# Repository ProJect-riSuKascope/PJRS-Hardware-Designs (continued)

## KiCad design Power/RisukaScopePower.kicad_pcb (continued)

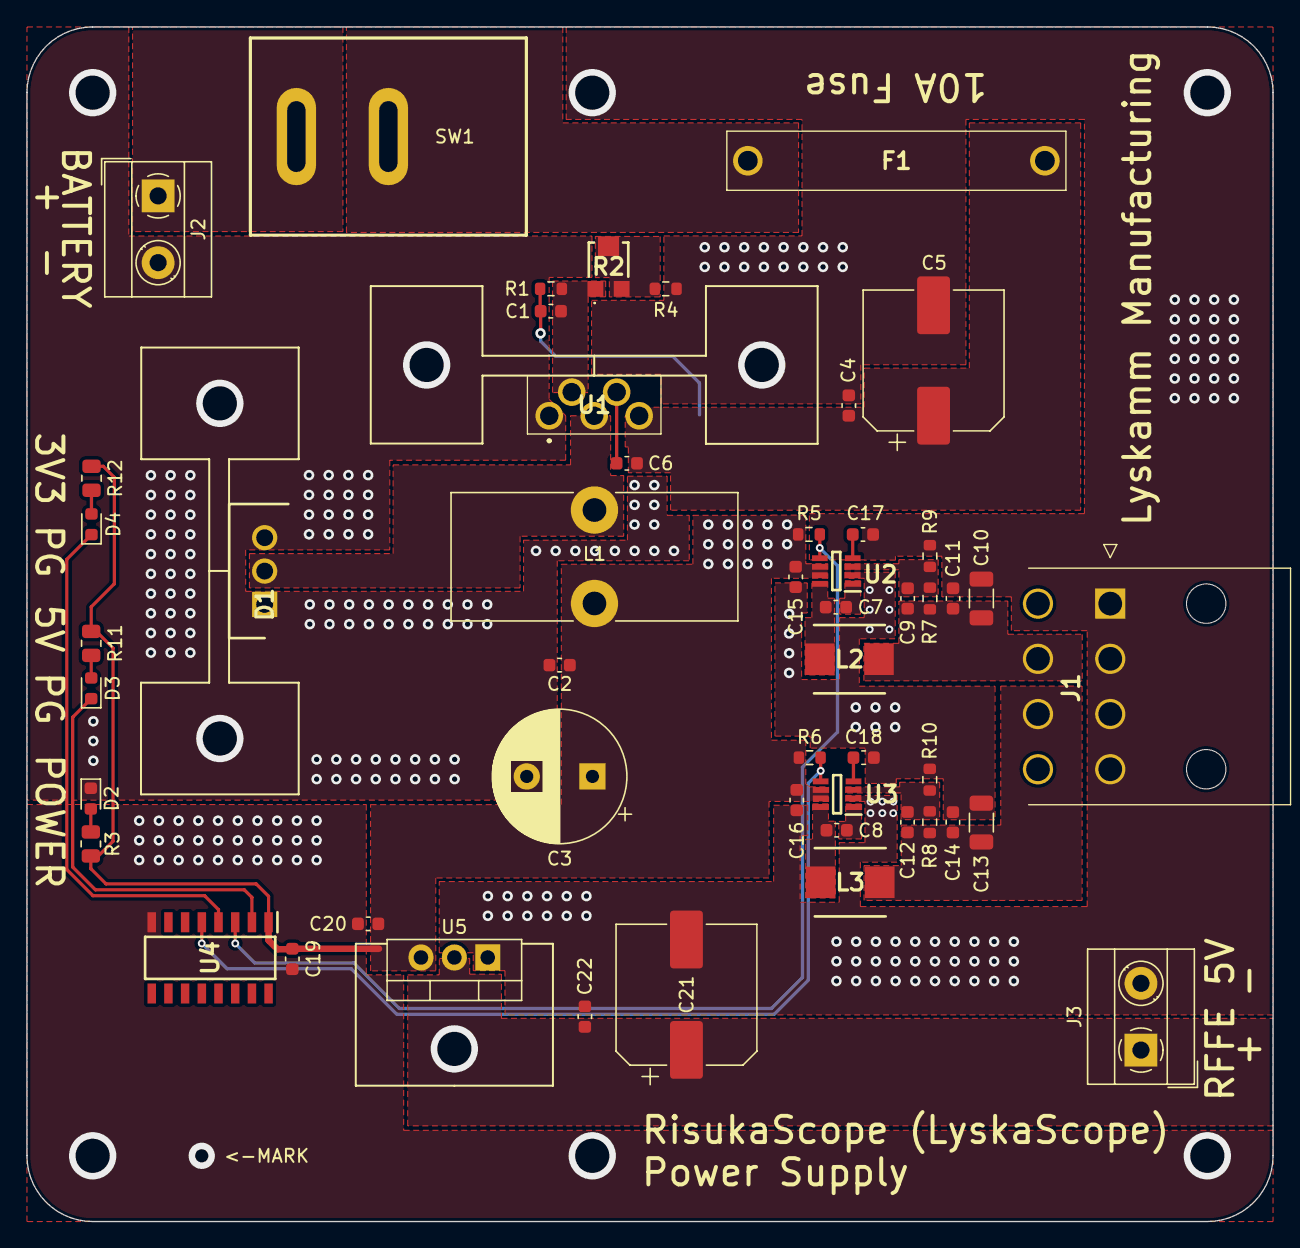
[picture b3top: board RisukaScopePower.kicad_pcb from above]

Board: 2 copper layers, 94.8 x 90.9 mm, 51 parts (0 on the bottom side), 27 nets.

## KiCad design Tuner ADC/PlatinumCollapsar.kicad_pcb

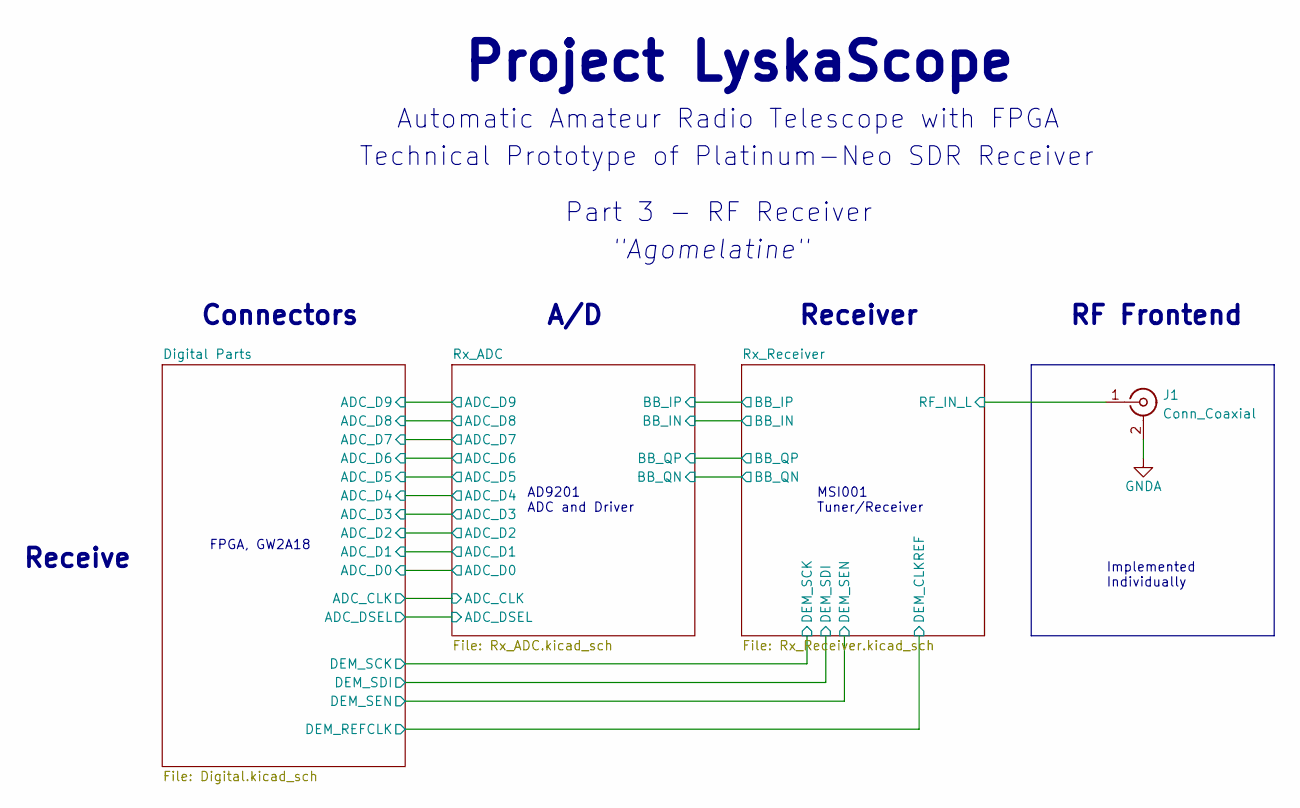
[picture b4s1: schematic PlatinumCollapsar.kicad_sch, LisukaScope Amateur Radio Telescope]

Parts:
J1: Conn_Coaxial; SMA_Samtec_SMA-J-P-X-ST-EM1_EdgeMount

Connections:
/Rx_Receiver/RF_IN_L: J1.1 (In); also elsewhere on the board

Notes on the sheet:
Connectors
Receive
FPGA, GW2A18
Technical Prototype of Platinum-Neo SDR Receiver
AD9201 ADC and Driver
Project LyskaScope
Receiver
Automatic Amateur Radio Telescope with FPGA
MSI001 Tuner/Receiver
Implemented Individually
RF Frontend
A/D
"Agomelatine"
Part 3 - RF Receiver

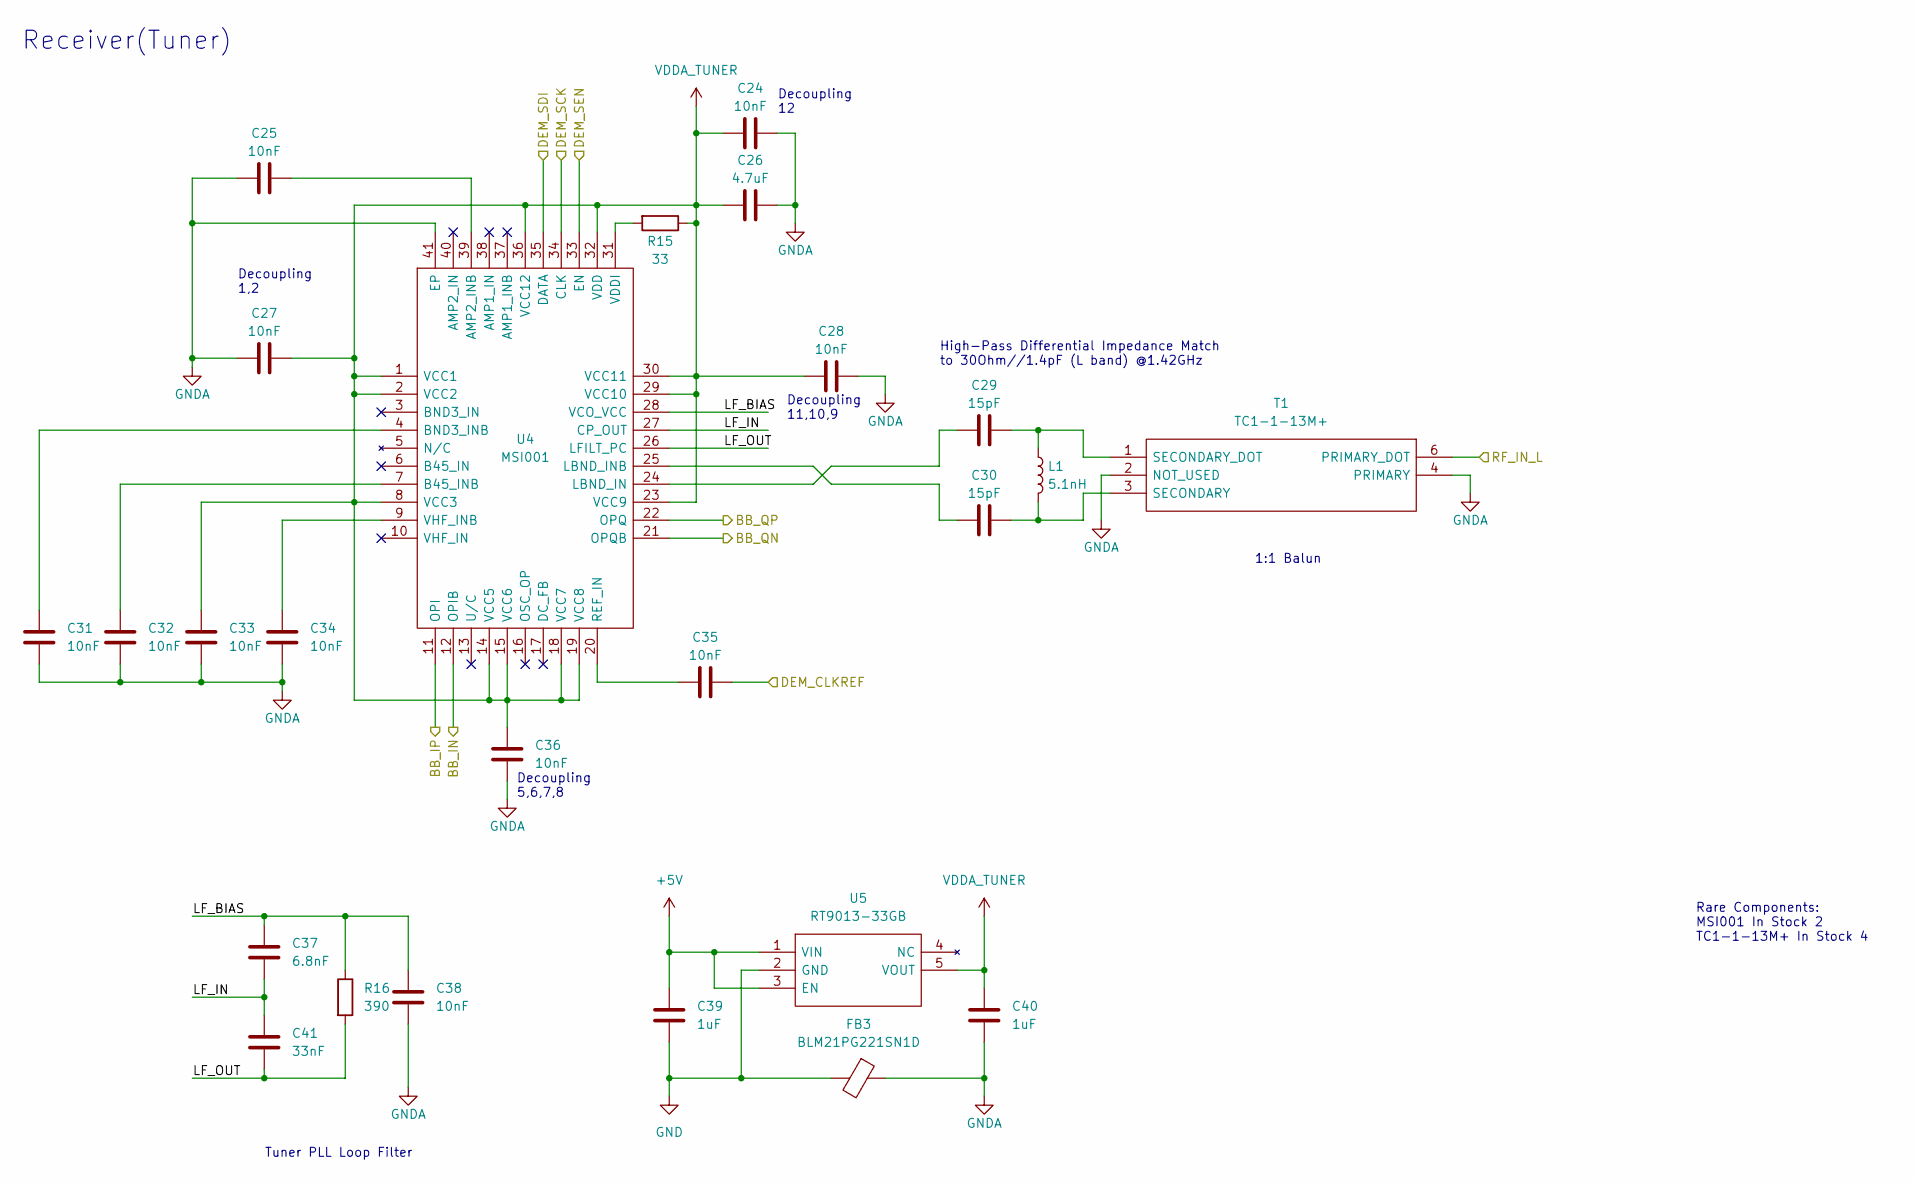
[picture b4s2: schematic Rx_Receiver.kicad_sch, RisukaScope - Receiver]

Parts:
C24, C25, C27, C28, C31, C32, C33, C34, C35, C36, C38: 10nF; C_0603_1608Metric
C26: 4.7uF; C_0603_1608Metric
C29, C30: 15pF; C_0603_1608Metric
C37: 6.8nF; C_0603_1608Metric
C39, C40: 1uF; C_0603_1608Metric
C41: 33nF; C_0603_1608Metric
FB3: BLM21PG221SN1D; L_0805_2012Metric
L1: 5.1nH; L_0603_1608Metric
R15: 33; R_0603_1608Metric
R16: 390; R_0603_1608Metric
T1: TC1-1-13M+; TC414; Manufacturer_Part_Number TC1-1-13M+; Mouser Part Number 139-TC1-1-13M
U4: MSI001; QFN50P600X600X90-41N-D; Manufacturer_Part_Number MSI001
U5: RT9013-33GB; SOT94P279X130-5N; Manufacturer_Part_Number RT9013-33GB

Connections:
+5V: C39.1, U5.1 (VIN), U5.3 (EN); also elsewhere on the board
/Digital Parts/DEM_REFCLK: C35.2; also elsewhere on the board
/Digital Parts/DEM_SCK: U4.34 (CLK); also elsewhere on the board
/Digital Parts/DEM_SDI: U4.35 (DATA); also elsewhere on the board
/Digital Parts/DEM_SEN: U4.33 (EN); also elsewhere on the board
/Rx_ADC/BB_IN: U4.12 (OPIB); also elsewhere on the board
/Rx_ADC/BB_IP: U4.11 (OPI); also elsewhere on the board
/Rx_ADC/BB_QN: U4.21 (OPQB); also elsewhere on the board
/Rx_ADC/BB_QP: U4.22 (OPQ); also elsewhere on the board
/Rx_Receiver/LF_BIAS: C37.1, C38.1, R16.1, U4.28 (VCO_VCC)
/Rx_Receiver/LF_IN: C37.2, C41.1, U4.27 (CP_OUT)
/Rx_Receiver/LF_OUT: C41.2, R16.2, U4.26 (LFILT_PC)
/Rx_Receiver/RF_IN_L: T1.6 (PRIMARY_DOT); also elsewhere on the board
GND: C39.2, FB3.2, U5.2 (GND); also elsewhere on the board
unnamed: C25.2, U4.39 (AMP2_INB)
unnamed: C29.1, U4.24 (LBND_IN)
unnamed: C29.2, L1.1, T1.1 (SECONDARY_DOT)
unnamed: C30.1, U4.25 (LBND_INB)
unnamed: C30.2, L1.2, T1.3 (SECONDARY)
unnamed: C31.1, U4.4 (BND3_INB)
unnamed: C32.1, U4.7 (B45_INB)
unnamed: C34.1, U4.9 (VHF_INB)
unnamed: C35.1, U4.20 (REF_IN)
unnamed: R15.2, U4.31 (VDDI)
VDDA_TUNER: C24.1, C26.1, C27.2, C28.1, C33.1, C36.1, C40.1, R15.1, U4.1 (VCC1), U4.2 (VCC2), U4.8 (VCC3), U4.14 (VCC5), U4.15 (VCC6), U4.18 (VCC7), U4.19 (VCC8), U4.23 (VCC9), U4.29 (VCC10), U4.30 (VCC11), U4.32 (VDD), U4.36 (VCC12), U5.5 (VOUT)

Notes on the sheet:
Decoupling 12
Decoupling 11,10,9
1:1 Balun
Receiver(Tuner)
Decoupling 5,6,7,8
Tuner PLL Loop Filter
High-Pass Differential Impedance Match to 30Ohm//1.4pF (L band) @1.42GHz
Rare Components: MSI001 In Stock 2 TC1-1-13M+ In Stock 4
Decoupling 1,2

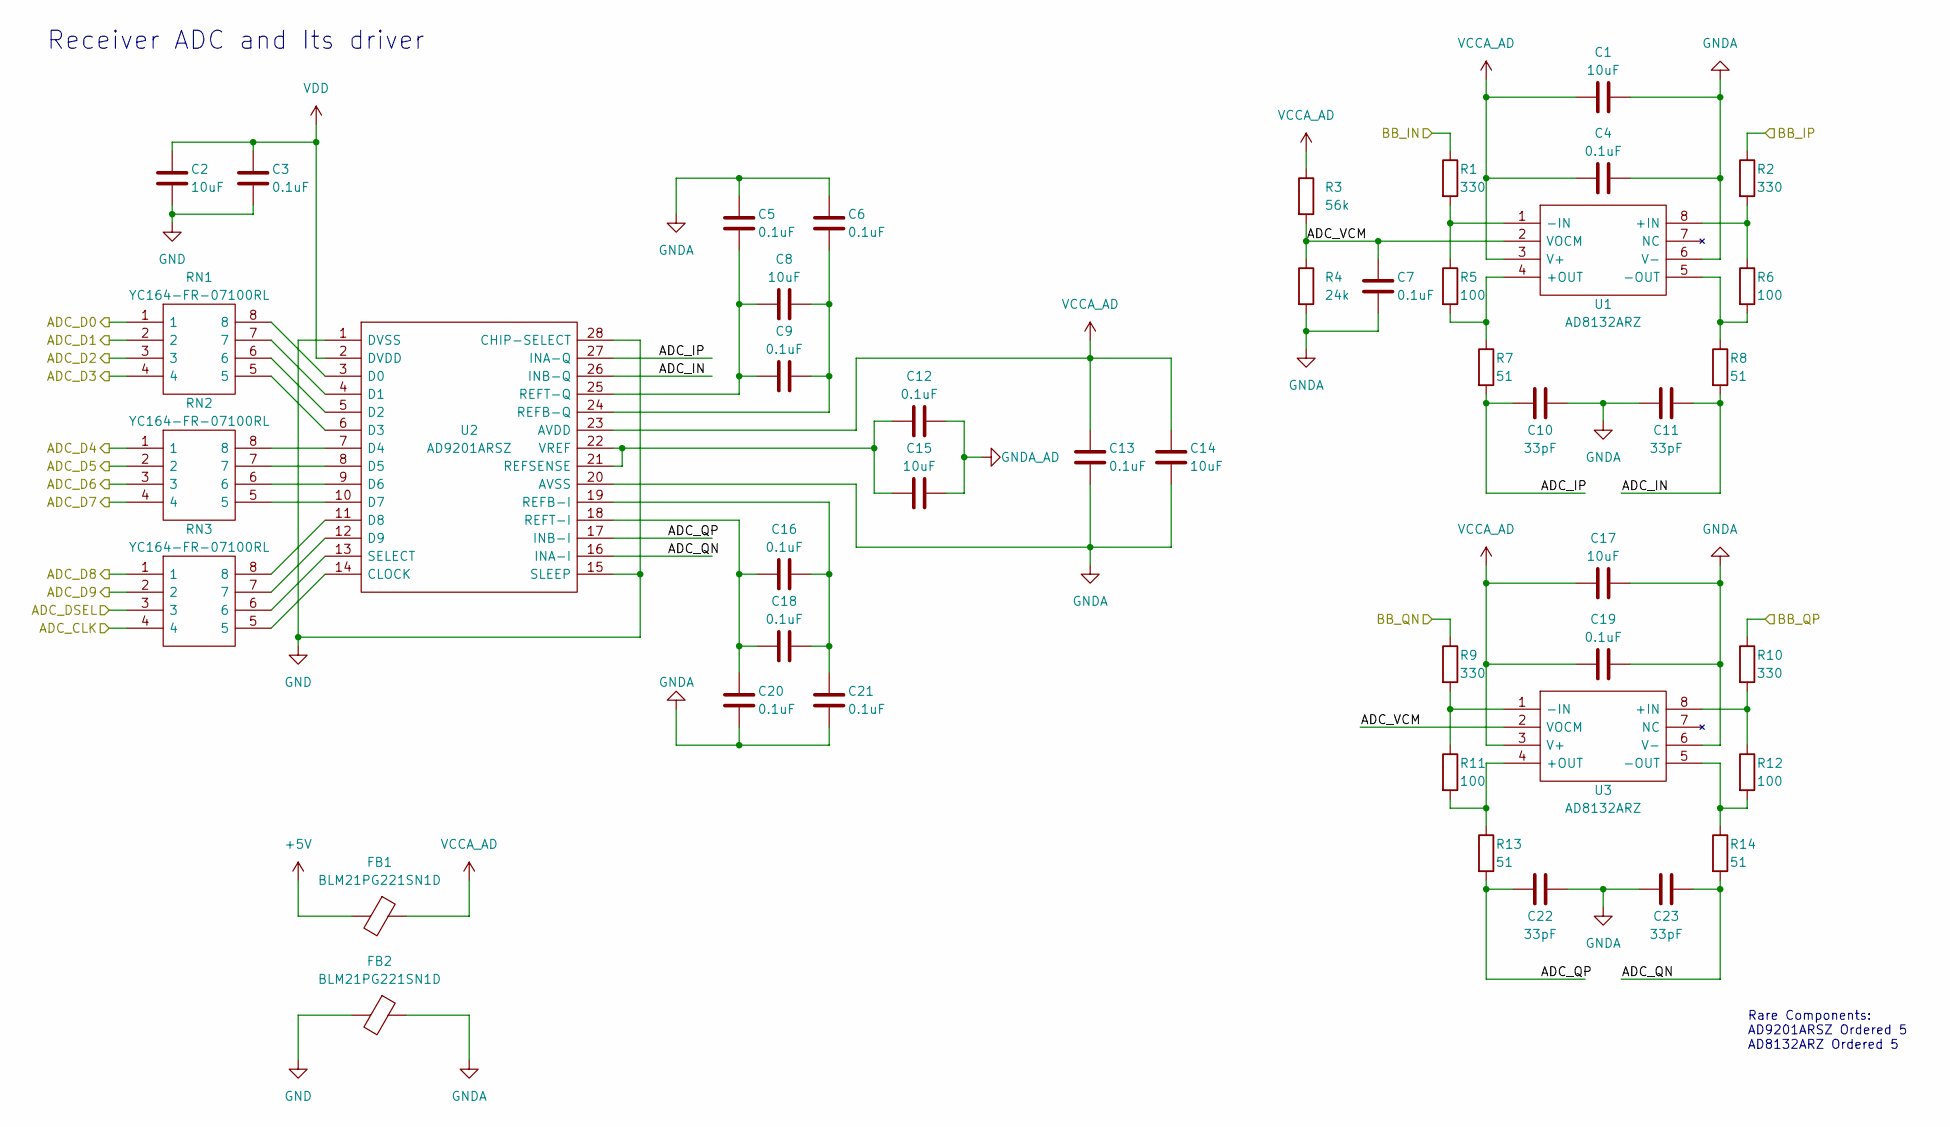
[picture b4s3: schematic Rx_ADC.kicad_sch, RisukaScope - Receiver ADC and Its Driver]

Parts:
C1, C2, C8, C14, C15, C17: 10uF; C_0603_1608Metric
C3, C4, C5, C6, C7, C9, C12, C13, C16, C18, C19, C20, C21: 0.1uF; C_0603_1608Metric
C10, C11, C22, C23: 33pF; C_0603_1608Metric
FB1, FB2: BLM21PG221SN1D; L_0805_2012Metric
R1, R2, R9, R10: 330; R_0603_1608Metric
R3: 56k; R_0603_1608Metric
R4: 24k; R_0603_1608Metric
R5, R6, R11, R12: 100; R_0603_1608Metric
R7, R8, R13, R14: 51; R_0603_1608Metric
RN1, RN2, RN3: YC164-FR-07100RL; YC164JR07220RL; Manufacturer_Part_Number YC164-FR-07100RL; Mouser Part Number 603-YC164-FR-07100RL
U1, U3: AD8132ARZ; SOIC127P600X175-8N; Manufacturer_Part_Number AD8132ARZ; Mouser Part Number 584-AD8132ARZ
U2: AD9201ARSZ; SOP65P777X198-28N; Manufacturer_Part_Number AD9201ARSZ; Mouser Part Number 584-AD9201ARSZ

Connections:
+5V: FB1.2; also elsewhere on the board
/Digital Parts/ADC_CLK: RN3.4; also elsewhere on the board
/Digital Parts/ADC_D0: RN1.1; also elsewhere on the board
/Digital Parts/ADC_D1: RN1.2; also elsewhere on the board
/Digital Parts/ADC_D2: RN1.3; also elsewhere on the board
/Digital Parts/ADC_D3: RN1.4; also elsewhere on the board
/Digital Parts/ADC_D4: RN2.1; also elsewhere on the board
/Digital Parts/ADC_D5: RN2.2; also elsewhere on the board
/Digital Parts/ADC_D6: RN2.3; also elsewhere on the board
/Digital Parts/ADC_D7: RN2.4; also elsewhere on the board
/Digital Parts/ADC_D8: RN3.1; also elsewhere on the board
/Digital Parts/ADC_D9: RN3.2; also elsewhere on the board
/Digital Parts/ADC_DSEL: RN3.3; also elsewhere on the board
/Rx_ADC/ADC_IN: C11.2, R8.2, U2.26 (INB-Q)
/Rx_ADC/ADC_IP: C10.1, R7.2, U2.27 (INA-Q)
/Rx_ADC/ADC_QN: C23.2, R14.2, U2.16 (INA-I)
/Rx_ADC/ADC_QP: C22.1, R13.2, U2.17 (INB-I)
/Rx_ADC/ADC_VCM: C7.1, R3.2, R4.1, U1.2 (VOCM), U3.2 (VOCM)
/Rx_ADC/BB_IN: R1.1; also elsewhere on the board
/Rx_ADC/BB_IP: R2.1; also elsewhere on the board
/Rx_ADC/BB_QN: R9.1; also elsewhere on the board
/Rx_ADC/BB_QP: R10.1; also elsewhere on the board
GND: C2.2, C3.2, FB2.2, U2.1 (DVSS), U2.15 (SLEEP), U2.28 (CHIP-SELECT); also elsewhere on the board
unnamed: C5.2, C8.1, C9.1, U2.25 (REFT-Q)
unnamed: C6.2, C8.2, C9.2, U2.24 (REFB-Q)
unnamed: C12.1, C15.1, U2.21 (REFSENSE), U2.22 (VREF)
unnamed: C16.1, C18.1, C20.1, U2.18 (REFT-I)
unnamed: C16.2, C18.2, C21.1, U2.19 (REFB-I)
unnamed: R1.2, R5.1, U1.1 (-IN)
unnamed: R2.2, R6.1, U1.8 (+IN)
unnamed: R5.2, R7.1, U1.4 (+OUT)
unnamed: R6.2, R8.1, U1.5 (-OUT)
unnamed: R10.2, R12.1, U3.8 (+IN)
unnamed: R9.2, R11.1, U3.1 (-IN)
unnamed: R11.2, R13.1, U3.4 (+OUT)
unnamed: R12.2, R14.1, U3.5 (-OUT)
unnamed: RN1.5, U2.6 (D3)
unnamed: RN1.6, U2.5 (D2)
unnamed: RN1.7, U2.4 (D1)
unnamed: RN1.8, U2.3 (D0)
unnamed: RN2.5, U2.10 (D7)
unnamed: RN2.6, U2.9 (D6)
unnamed: RN2.7, U2.8 (D5)
unnamed: RN2.8, U2.7 (D4)
unnamed: RN3.5, U2.14 (CLOCK)
unnamed: RN3.6, U2.13 (SELECT)
unnamed: RN3.7, U2.12 (D9)
unnamed: RN3.8, U2.11 (D8)
VCCA_AD: C1.1, C4.1, C13.1, C14.1, C17.1, C19.1, FB1.1, R3.1, U1.3 (V+), U2.23 (AVDD), U3.3 (V+)
VDD: C2.1, C3.1, U2.2 (DVDD); also elsewhere on the board

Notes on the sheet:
Rare Components: AD9201ARSZ Ordered 5 AD8132ARZ Ordered 5
Receiver ADC and Its driver

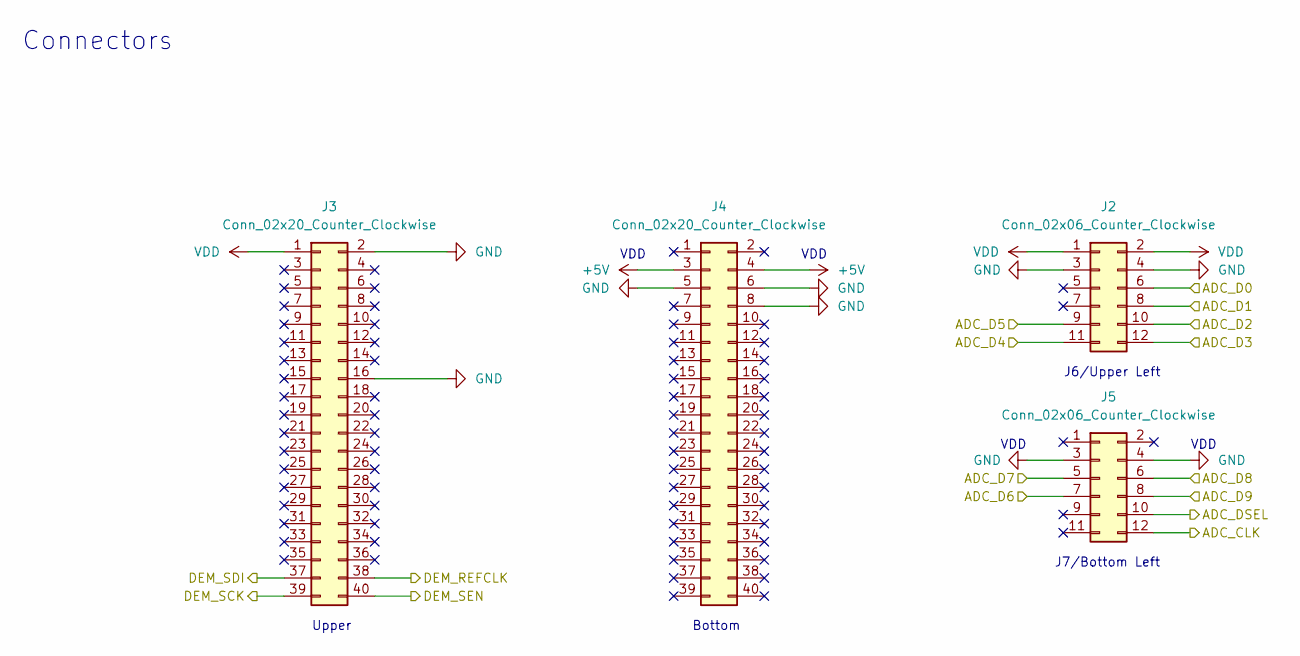
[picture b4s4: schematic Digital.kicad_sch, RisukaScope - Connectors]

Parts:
J2, J5: Conn_02x06_Counter_Clockwise; PinHeader_2x06_P2.54mm_Vertical
J3, J4: Conn_02x20_Counter_Clockwise; PinHeader_2x20_P2.54mm_Vertical

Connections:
+5V: J4.3, J4.4; also elsewhere on the board
/Digital Parts/ADC_CLK: J5.12; also elsewhere on the board
/Digital Parts/ADC_D0: J2.6; also elsewhere on the board
/Digital Parts/ADC_D1: J2.8; also elsewhere on the board
/Digital Parts/ADC_D2: J2.10; also elsewhere on the board
/Digital Parts/ADC_D3: J2.12; also elsewhere on the board
/Digital Parts/ADC_D4: J2.11; also elsewhere on the board
/Digital Parts/ADC_D5: J2.9; also elsewhere on the board
/Digital Parts/ADC_D6: J5.7; also elsewhere on the board
/Digital Parts/ADC_D7: J5.5; also elsewhere on the board
/Digital Parts/ADC_D8: J5.6; also elsewhere on the board
/Digital Parts/ADC_D9: J5.8; also elsewhere on the board
/Digital Parts/ADC_DSEL: J5.10; also elsewhere on the board
/Digital Parts/DEM_REFCLK: J3.38; also elsewhere on the board
/Digital Parts/DEM_SCK: J3.39; also elsewhere on the board
/Digital Parts/DEM_SDI: J3.37; also elsewhere on the board
/Digital Parts/DEM_SEN: J3.40; also elsewhere on the board
GND: J2.3, J2.4, J3.2, J3.16, J4.5, J4.6, J4.8, J5.3, J5.4; also elsewhere on the board
VDD: J2.1, J2.2, J3.1; also elsewhere on the board

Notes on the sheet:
Upper
J7/Bottom Left
VDD
J6/Upper Left
Connectors
Bottom

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
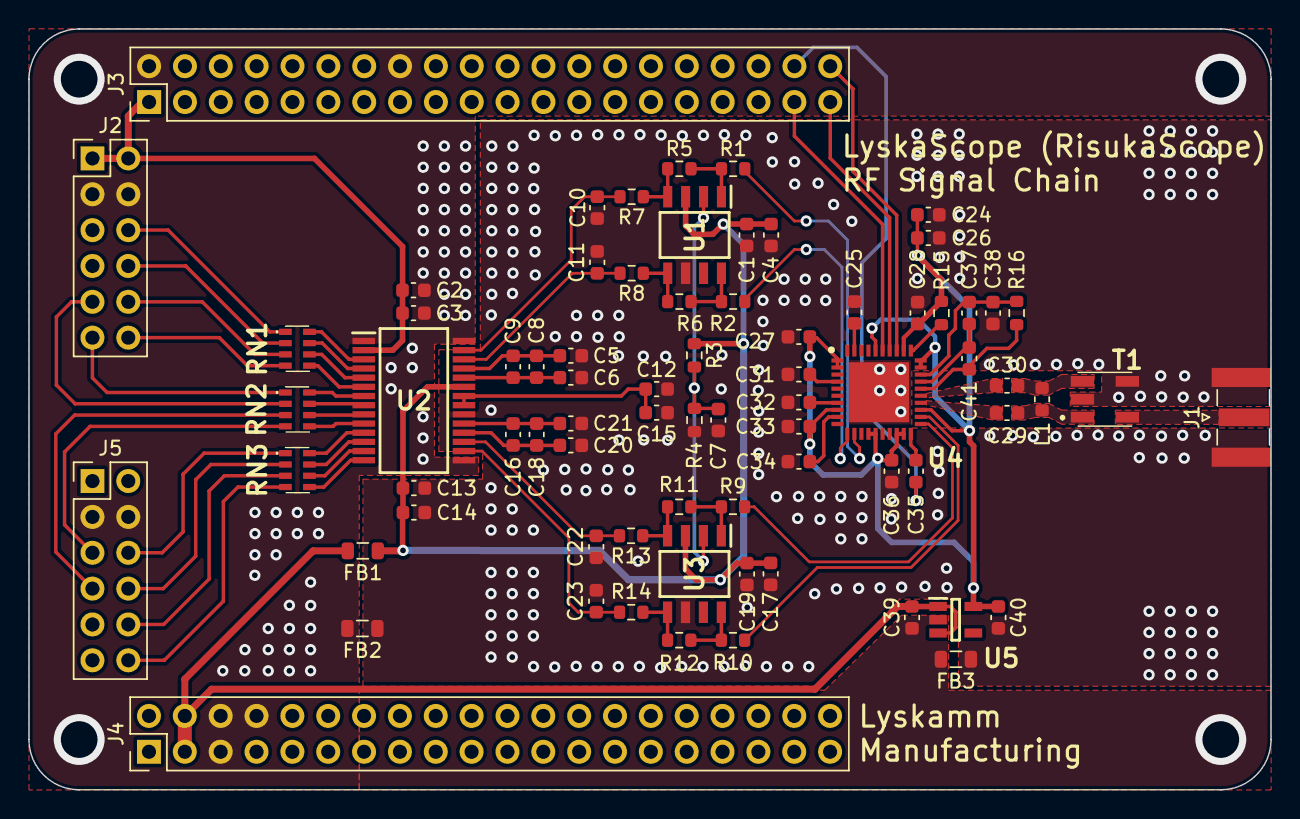
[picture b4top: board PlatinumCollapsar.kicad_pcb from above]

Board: 2 copper layers, 88.0 x 53.9 mm, 75 parts (0 on the bottom side), 70 nets.

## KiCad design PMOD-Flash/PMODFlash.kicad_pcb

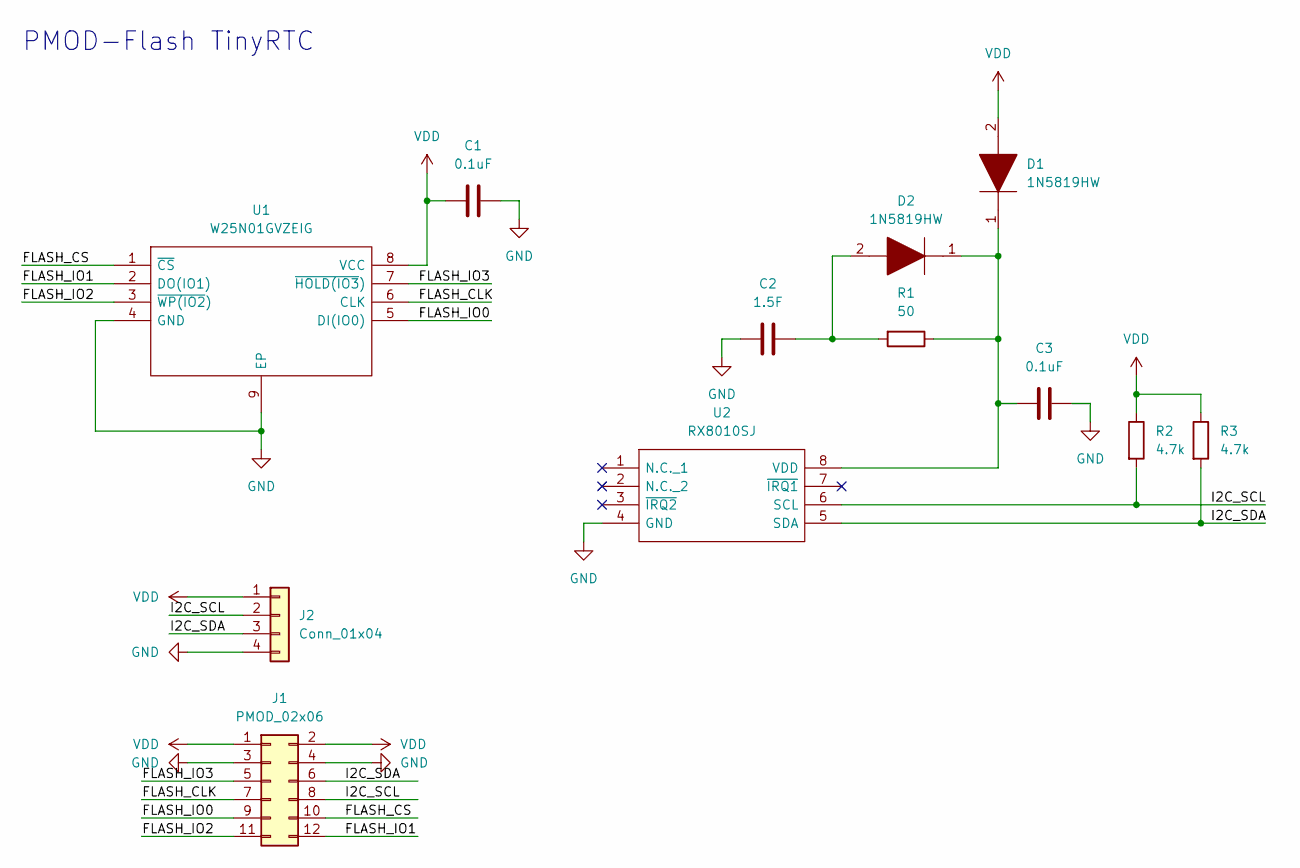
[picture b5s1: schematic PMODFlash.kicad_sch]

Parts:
C1, C3: 0.1uF; C_0603_1608Metric
C2: 1.5F; EECS5R5V155N
D1, D2: 1N5819HW; SOD3716X145N; Manufacturer_Part_Number 1N5819HW; Mouser Part Number N/A
J1: PMOD_02x06; PinHeader_2x06_P2.54mm_Vertical
J2: Conn_01x04; PinHeader_1x04_P2.54mm_Vertical
R1: 50; R_0603_1608Metric
R2, R3: 4.7k; R_0603_1608Metric
U1: W25N01GVZEIG; SON127P800X600X80-9N-D; Manufacturer_Part_Number W25N01GVZEIG; Mouser Part Number 454-W25N01GVZEIG
U2: RX8010SJ; SOIC127P600X265-8N; Manufacturer_Part_Number RX8010SJ

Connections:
/FLASH_CLK: J1.7, U1.6 (CLK)
/FLASH_CS: J1.10, U1.1 (~CS)
/FLASH_IO0: J1.9, U1.5 (DI(IO0))
/FLASH_IO1: J1.12, U1.2 (DO(IO1))
/FLASH_IO2: J1.11, U1.3 (~WP(IO2))
/FLASH_IO3: J1.5, U1.7 (~HOLD(IO3))
/I2C_SCL: J1.8, J2.2, R2.2, U2.6 (SCL)
/I2C_SDA: J1.6, J2.3, R3.2, U2.5 (SDA)
GND: C1.1, C2.2, C3.1, J1.3, J1.4, J2.4, U1.4 (GND), U1.9 (EP), U2.4 (GND)
unnamed: C2.1, D2.2, R1.2
unnamed: C3.2, D1.1, D2.1, R1.1, U2.8 (VDD)
VDD: C1.2, D1.2, J1.1, J1.2, J2.1, R2.1, R3.1, U1.8 (VCC)

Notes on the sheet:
PMOD-Flash TinyRTC

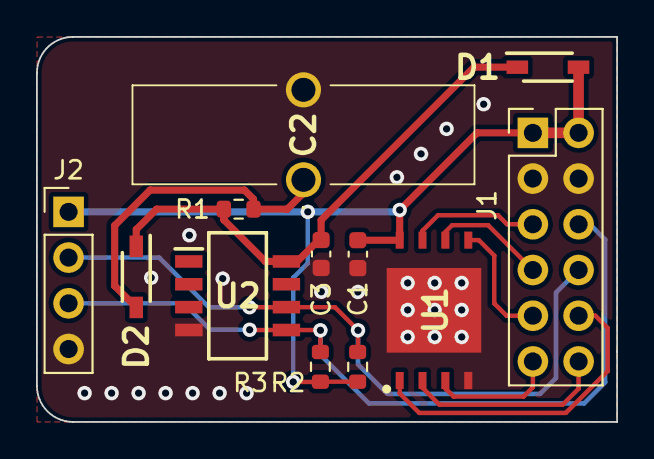
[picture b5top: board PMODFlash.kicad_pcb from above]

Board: 2 copper layers, 32.2 x 21.4 mm, 12 parts (0 on the bottom side), 12 nets.
